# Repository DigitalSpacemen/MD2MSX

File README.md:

## About MD2MSX

MD2MSX is a joystick adapter to connect a Mega Drive / Genesis controller to an MSX computer. Software that works with the [JoyMega](https://frs.badcoffee.info/hardware/joymega-en.html) adapter should also work with the MD2MSX.

This is a hardware project by retro computing enthusiasts. We are not experts. **USE AT YOUR OWN RISK!** Please make sure to read the [Usage Notes](#important-usage-notes) first.

### Why another joystick adapter?

The JoyMega works great with official controllers. However, many 3rd-party controllers don't implement the controller protocol very accurately. Here's some examples of possible issues:

- 8BitDo wireless receivers working in 3-/6-button mode, but not working as a plain MSX joystick.
- Retro-Bit wired controllers and receivers not working in 6-button mode.
- Unbranded 3rd party controller switching to a permanent 3-button mode when the Mode button is pressed in-game.

Please check our [Controller Notes](Controller%20Notes.md) for more detailed information.

### How does MD2MSX work?

Our proposed solution places an Arduino inbetween the controller and the MSX. This Arduino robustly reads the controller on the input side. On the output side, it implements the controller protocol more accurately than the 3rd-party controllers. We designed a simple PCB for this purpose with two DB-9 (or DE-9) ports and header pins to plug in an Arduino Nano. MD2MSX also implements the JoyMega pin mapping and select signal inversion. MD2MSX should be connected to the MSX directly; do not connect it to the JoyMega.

*MD2MSX with a cable soldered directly to the board in place of the 2nd DB-9 port.*

### How do I make one?

Apart from the MD2MSX PCB you need the following components:

- 1x male DB-9 port (matching the footprint on the PCB).
- 1x female DB-9 port (matching the footprint on the PCB) **OR** a cable with a female DB-9 at the end, to solder directly to the board.
- 2x BAT85 DO-35 diodes. Other switching diodes should also work, but have not been tested.
- 2x 15-pin female header pins.
- 1x Arduino Nano (or clone) with male header pins.

For the hardware, the [KiCad](https://www.kicad.org/) design files can be found in the hardware/ directory. KiCad is used to produce Gerber files for upload to your favourite PCB manufacturer.

The firmware resides in firmware/ and is compiled with [PlatformIO](https://platformio.org/).

### Important usage notes

Do not connect the MD2MSX to both an MSX computer and USB at the same time, even if only one of the devices is powered on!

If you're planning to use a wireless receiver, the current draw may exceed the 50mA rating of the MSX joystick port. Make sure your particular MSX computer can handle this.

### Some things to consider if you decide to build one

If you build it without the cable directly attached, you would either need to obtain a straight-through DB-9 to DB-9 cable, or figure out a way to plug the board directly into the MSX computer. The latter may prove to be difficult.

Ensure the cable going to the MSX computer has a sufficient gauge for the current needed by the Arduino and the controller, especially if you're planning to use a wireless receiver. If you do end up using a cable with thin wires, we recommend making the cable as short as possible.

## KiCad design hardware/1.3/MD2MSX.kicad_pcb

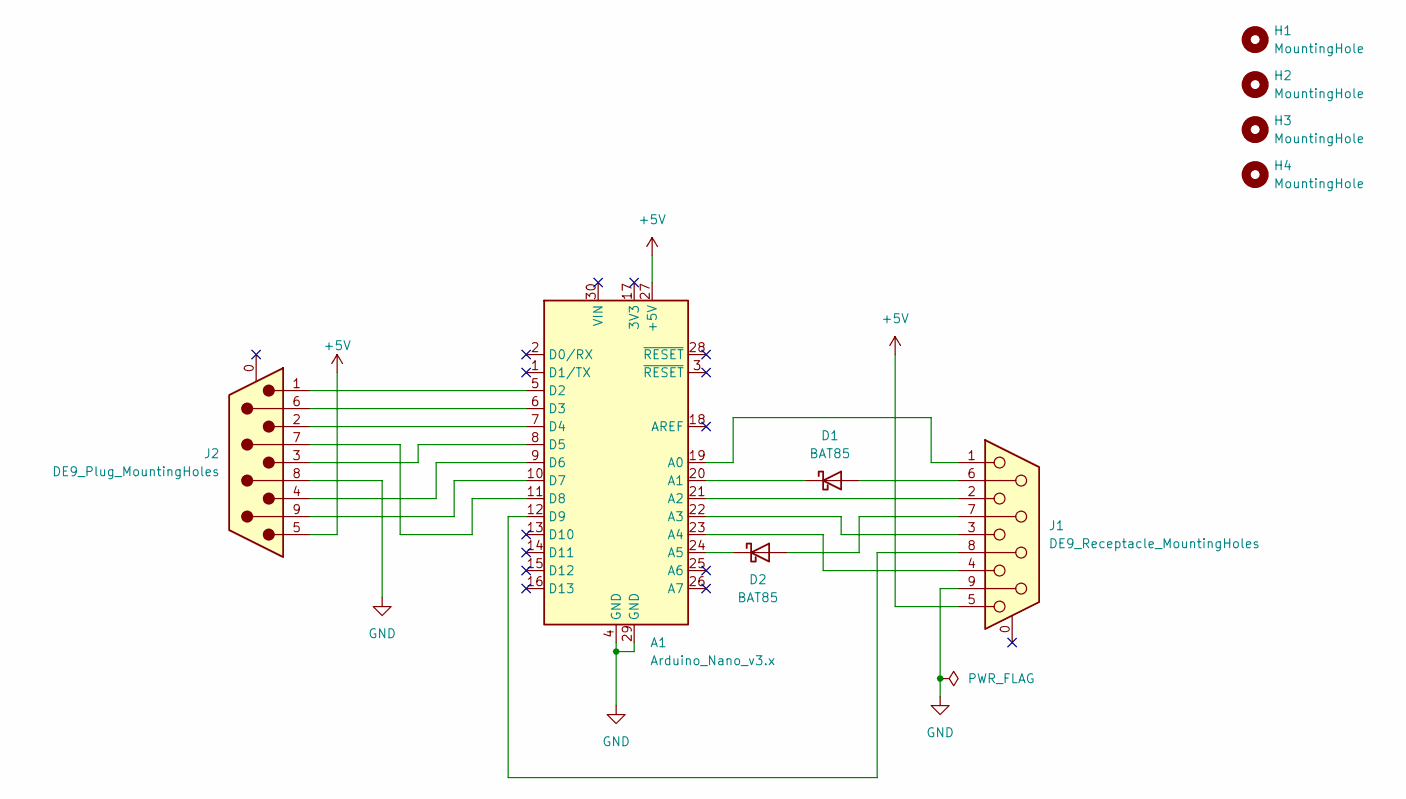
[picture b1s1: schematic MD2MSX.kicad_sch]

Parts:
A1: Arduino_Nano_v3.x; Arduino_Nano
D1, D2: BAT85; D_DO-35_SOD27_P7.62mm_Horizontal
H1, H2, H3, H4: MountingHole; MountingHole_3.2mm_M3
J1: DE9_Receptacle_MountingHoles; DSUB-9_Female_Horizontal_P2.77x2.84mm_EdgePinOffset9.90mm_H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
J2: DE9_Plug_MountingHoles; DSUB-9_Male_Horizontal_P2.77x2.84mm_EdgePinOffset9.90mm_Hou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

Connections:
+5V: A1.27 (+5V), J1.5, J2.5
GND: A1.4 (GND), A1.29 (GND), J1.9, J2.8
unnamed: A1.19 (A0), J1.1
unnamed: A1.20 (A1), D1.1 (K)
unnamed: A1.21 (A2), J1.2
unnamed: A1.22 (A3), J1.3
unnamed: A1.23 (A4), J1.4
unnamed: A1.24 (A5), D2.1 (K)
unnamed: A1.5 (D2), J2.1
unnamed: A1.6 (D3), J2.6
unnamed: A1.7 (D4), J2.2
unnamed: A1.8 (D5), J2.3
unnamed: A1.9 (D6), J2.4
unnamed: A1.10 (D7), J2.9
unnamed: A1.11 (D8), J2.7
unnamed: A1.12 (D9), J1.8
unnamed: D1.2 (A), J1.6
unnamed: D2.2 (A), J1.7

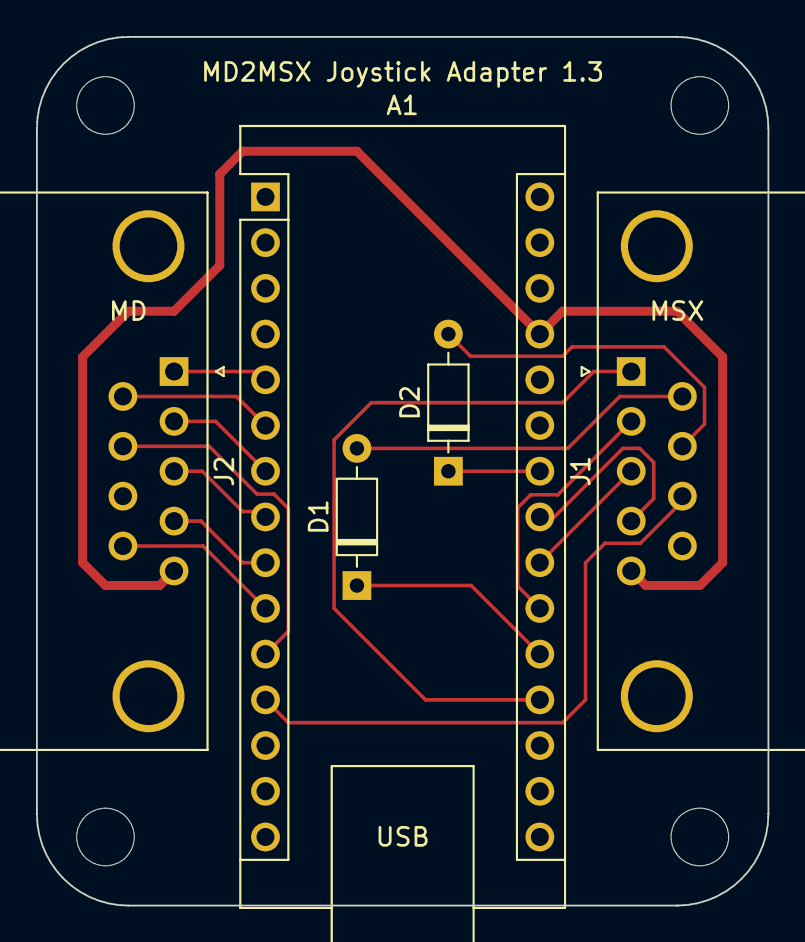
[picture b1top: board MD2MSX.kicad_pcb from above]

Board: 2 copper layers, 40.6 x 48.3 mm, 9 parts (0 on the bottom side), 18 nets.

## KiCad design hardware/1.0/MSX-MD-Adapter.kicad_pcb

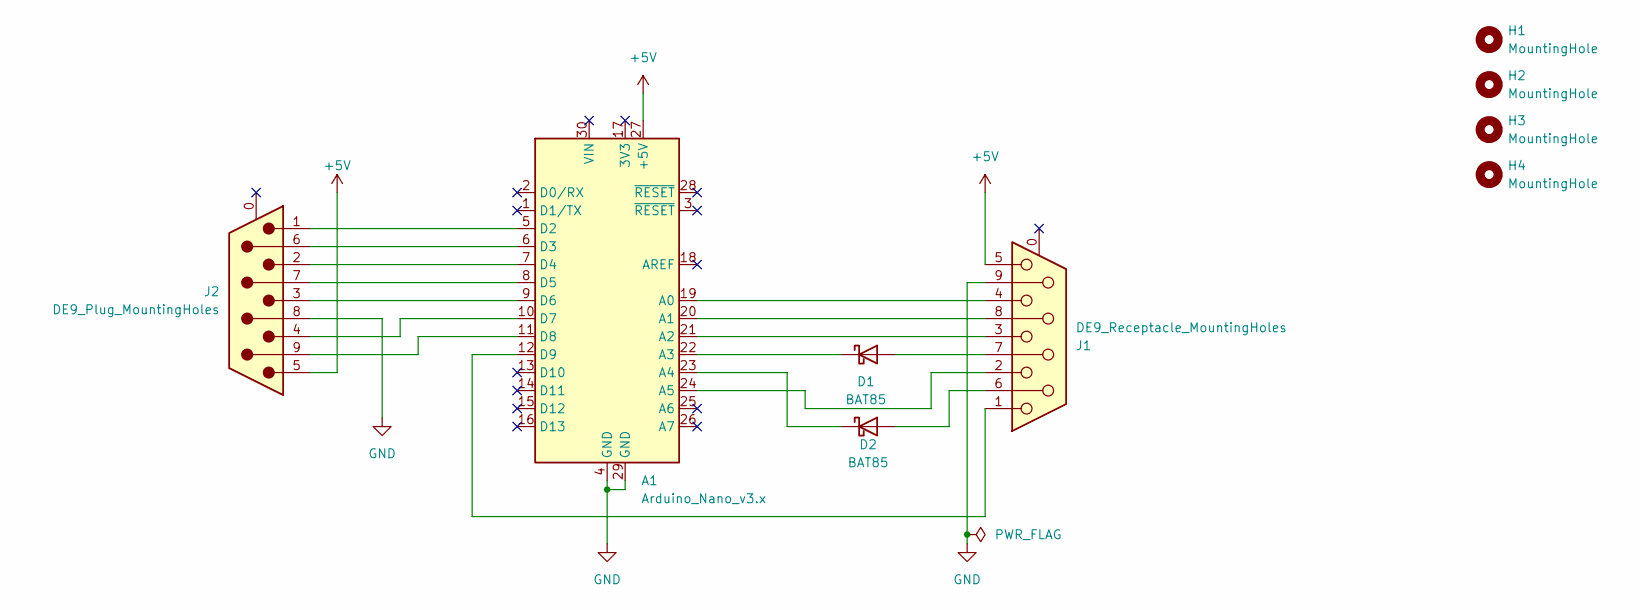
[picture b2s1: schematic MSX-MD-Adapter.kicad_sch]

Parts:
A1: Arduino_Nano_v3.x; Arduino_Nano
D1, D2: BAT85; D_DO-35_SOD27_P7.62mm_Horizontal
H1, H2, H3, H4: MountingHole; MountingHole_3.2mm_M3
J1: DE9_Receptacle_MountingHoles; DSUB-9_Female_Horizontal_P2.77x2.84mm_EdgePinOffset9.90mm_H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
J2: DE9_Plug_MountingHoles; DSUB-9_Male_Horizontal_P2.77x2.84mm_EdgePinOffset9.90mm_Hou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

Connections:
+5V: A1.27 (+5V), J1.5, J2.5
GND: A1.4 (GND), A1.29 (GND), J1.9, J2.8
unnamed: A1.19 (A0), J1.4
unnamed: A1.20 (A1), J1.8
unnamed: A1.21 (A2), J1.3
unnamed: A1.22 (A3), D1.1 (K)
unnamed: A1.23 (A4), D2.1 (K)
unnamed: A1.24 (A5), J1.2
unnamed: A1.5 (D2), J2.1
unnamed: A1.6 (D3), J2.6
unnamed: A1.7 (D4), J2.2
unnamed: A1.8 (D5), J2.7
unnamed: A1.9 (D6), J2.3
unnamed: A1.10 (D7), J2.4
unnamed: A1.11 (D8), J2.9
unnamed: A1.12 (D9), J1.1
unnamed: D1.2 (A), J1.7
unnamed: D2.2 (A), J1.6

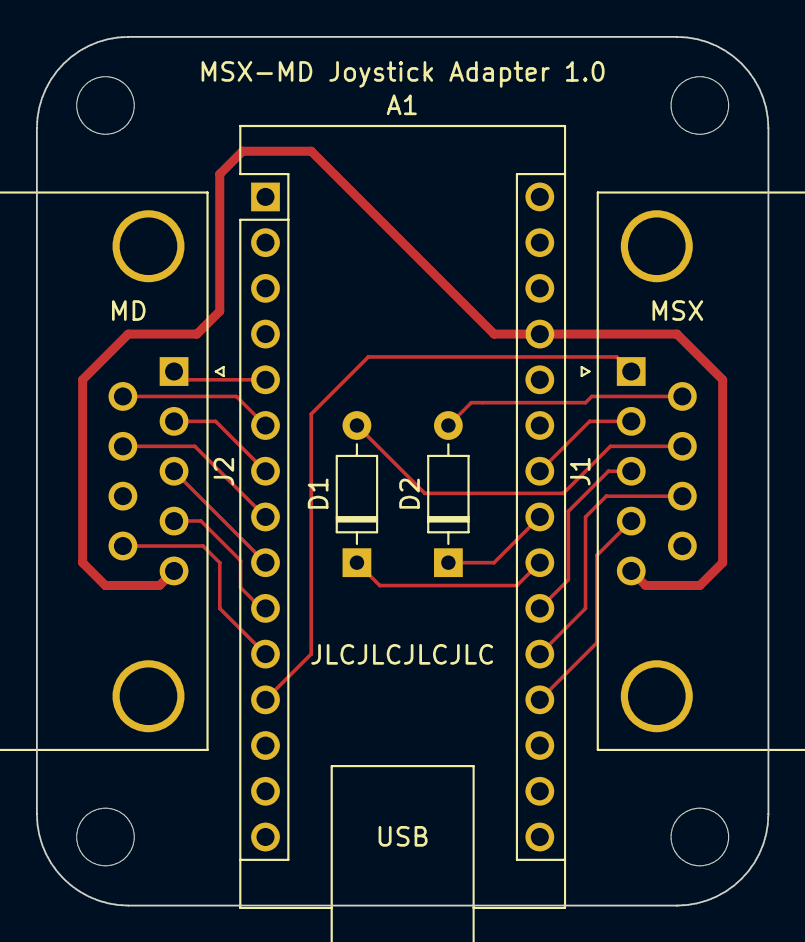
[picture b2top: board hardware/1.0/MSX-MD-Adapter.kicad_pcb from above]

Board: 2 copper layers, 40.6 x 48.3 mm, 9 parts (0 on the bottom side), 18 nets.

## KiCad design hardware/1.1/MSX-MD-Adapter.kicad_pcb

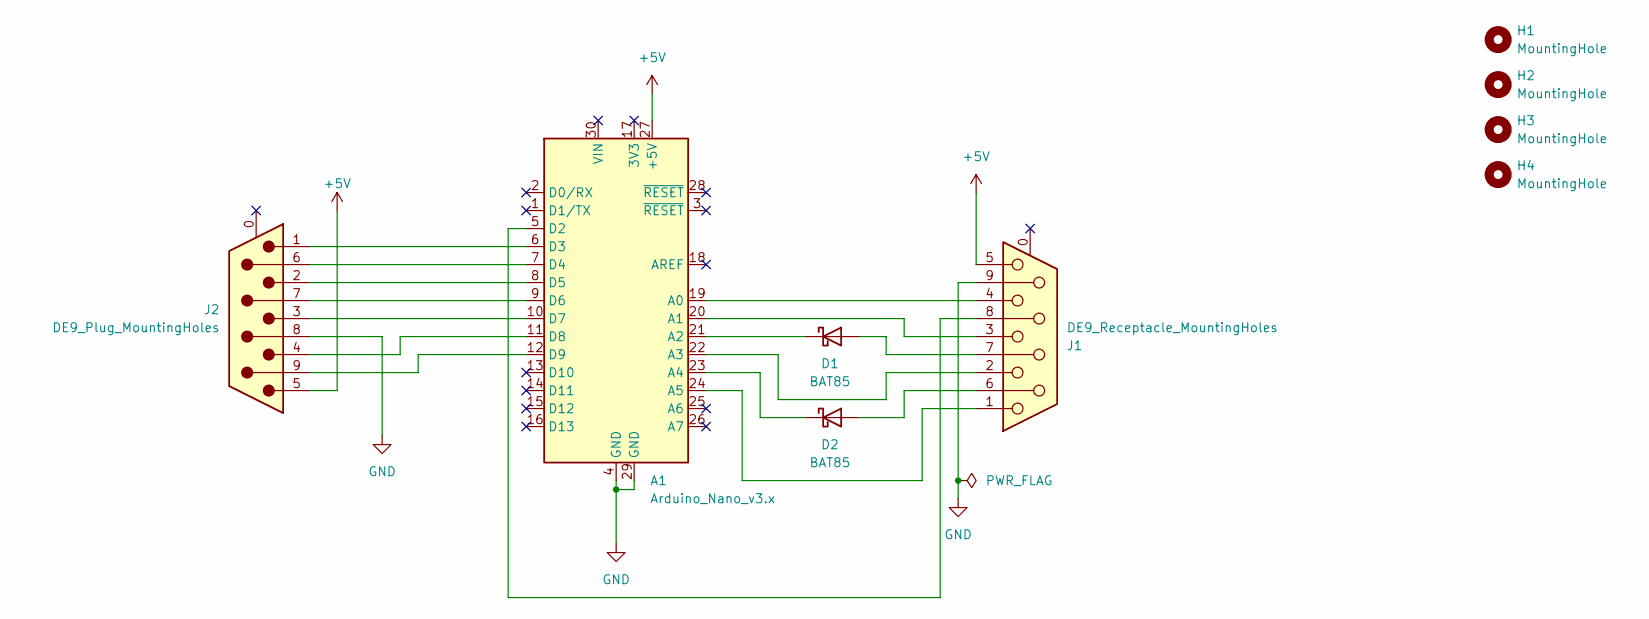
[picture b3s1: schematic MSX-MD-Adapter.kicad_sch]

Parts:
A1: Arduino_Nano_v3.x; Arduino_Nano
D1, D2: BAT85; D_DO-35_SOD27_P7.62mm_Horizontal
H1, H2, H3, H4: MountingHole; MountingHole_3.2mm_M3
J1: DE9_Receptacle_MountingHoles; DSUB-9_Female_Horizontal_P2.77x2.84mm_EdgePinOffset9.90mm_H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
J2: DE9_Plug_MountingHoles; DSUB-9_Male_Horizontal_P2.77x2.84mm_EdgePinOffset9.90mm_Hou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

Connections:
+5V: A1.27 (+5V), J1.5, J2.5
GND: A1.4 (GND), A1.29 (GND), J1.9, J2.8
unnamed: A1.19 (A0), J1.4
unnamed: A1.20 (A1), J1.3
unnamed: A1.21 (A2), D1.1 (K)
unnamed: A1.22 (A3), J1.2
unnamed: A1.23 (A4), D2.1 (K)
unnamed: A1.24 (A5), J1.1
unnamed: A1.5 (D2), J1.8
unnamed: A1.6 (D3), J2.1
unnamed: A1.7 (D4), J2.6
unnamed: A1.8 (D5), J2.2
unnamed: A1.9 (D6), J2.7
unnamed: A1.10 (D7), J2.3
unnamed: A1.11 (D8), J2.4
unnamed: A1.12 (D9), J2.9
unnamed: D1.2 (A), J1.7
unnamed: D2.2 (A), J1.6

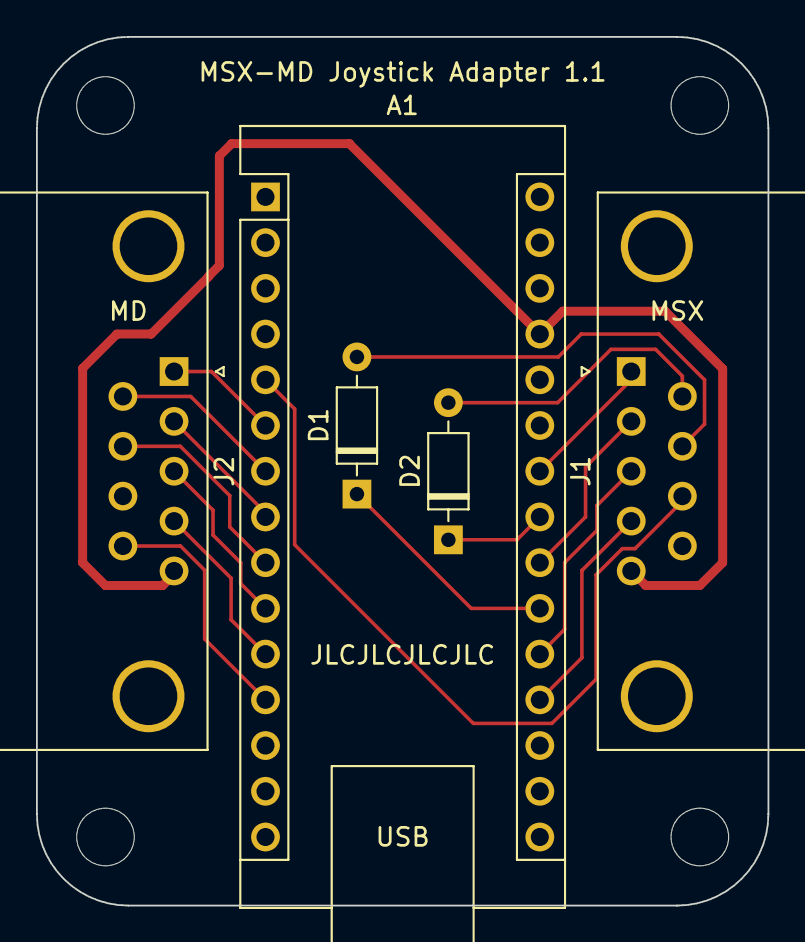
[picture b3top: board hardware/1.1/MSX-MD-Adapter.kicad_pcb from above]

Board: 2 copper layers, 40.6 x 48.3 mm, 9 parts (0 on the bottom side), 18 nets.

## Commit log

2024-01-17 Replace DEBUG #define with constexpr
2024-01-17 Cleanup
2024-01-18 Add firmware for PCB 1.2
2024-01-18 Rename 'debug' to 'tester'
2024-01-21 Use pinModeFast. Decreases binary size
2024-01-23 Custom pin code
2024-01-23 Add comments
2024-01-26 Add controller test
2024-02-01 Update comments
2024-02-01 Rename file
2024-02-01 PCB version 1.3
2024-02-01 Rename directories
2024-02-01 PIO overwrites extensions.json with LF endings
2024-02-01 Remove old board versions
2024-02-19 Add env for new nano bootloader
2024-08-04 Add case
